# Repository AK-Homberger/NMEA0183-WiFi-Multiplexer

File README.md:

# NMEA0183 WiFi Multiplexer with ESP8266 (D1 Mini)

# Caution! 
# ----------------------------
This is an updated version (0.2) with pins changed from D7/D8 to D6/D7 to avoid boot problems (see Issues).
If you ordered already a version 1.0 PCB, then just cut the connection to D8 (e.g. with a knife) and solder a wire to D6 pin on D1 Mini. The updated software (version 0.2) will work then. But with changed serial line numbers from #1 to #2 and vice versa.
# ----------------------------

The project reads NMEA0183 messages from two serial (RS232) inputs and forwards multiplexed messages to USB-Serial and WLAN as UDP broadcast.

The multiplexer is powered either from USB connection or with 12 Volt via DC-DC converter.
ESP8266 is using Software Serial on ports D6 and D7.

Main purpose is to provide GPS and AIS information wirelessly to a tablet/smartphone for navigation.
Works with Navionics app (configure UDP connection with Host: x.y.z.255 and Port: 4444).

There is also a [software version](https://github.com/AK-Homberger/NMEA0183-WiFi-Multiplexer/tree/main/NMEA083-Parser-WiFi-Multiplexer) that is parsing the messages and can suppress certain messages. This version needs this additional NMEA0183 libray: https://github.com/ttlappalainen/NMEA0183

Just change the settings in the [programm](https://github.com/AK-Homberger/NMEA0183-WiFi-Multiplexer/blob/main/NMEA083-WiFi-Multiplexer/NMEA083-WiFi-Multiplexer.ino) according to your needs:

```
// Change these values only
// ------------------------------------------------------------------------
#define AP 0             // Set to 1 to act as Access Point, 0 as client 

const char *ssid      = "ssid";           // Set WLAN name
const char *password  = "password";      // Set password

const char *udpAddress = "192.168.4.255"; // Set network address for broadcast
const int udpPort = 4444;                 // UDP port

#define BaudRate1 4800   // Baud rate for serial#1
#define BaudRate2 38400  // Baud rate for serial#2

// -------------------------------------------------------------------------

```

KiCad files are available to change/extend and to create a [PCB](https://github.com/AK-Homberger/NMEA0183-WiFi-Multiplexer/blob/main/KiCadNMEA0183-WiFi-Multiplexer/PCB.pdf).

## Parts

- U1: [ESP8266 (D1Mini)](https://www.reichelt.de/de/en/d1-mini-esp8266-v3-0-d1-mini-p253978.html?&nbc=1)
- U2: [Max232](https://www.reichelt.de/de/en/rs232-driver-dil-16-max-232-cpe-p11216.html?&nbc=1)
- C1-C4: 4* [Capacitor 1µF](https://www.reichelt.de/de/en/tantalum-capacitor-rm-2-5-1-0-f-35-v-tantal-1-0-35-p20330.html?&nbc=1)
- J1-J3: 3* [Connector](https://www.reichelt.de/de/en/2-pin-terminal-strip-spacing-5-08-akl-101-02-p36605.html?&nbc=1)
- U3: [DC-DC Converter](https://www.reichelt.de/de/en/dc-dc-converter-5-v-1-a-single-r-78e50-10-p177268.html?&nbc=1)
- [Board](https://aisler.net/p/EZUNBBJG) @Aisler.net

## Updates
- 10.11.2022 - Version 0.3: Corrected line end handling to avaid duplication of messages sent (see Issues).
- 01.10.2021 - Version 0.2: Changed pins from D/D8 to D6/D7 to avoid boot problems (see Issues).
- 06.03.2021 - Version 0.1: Initial version

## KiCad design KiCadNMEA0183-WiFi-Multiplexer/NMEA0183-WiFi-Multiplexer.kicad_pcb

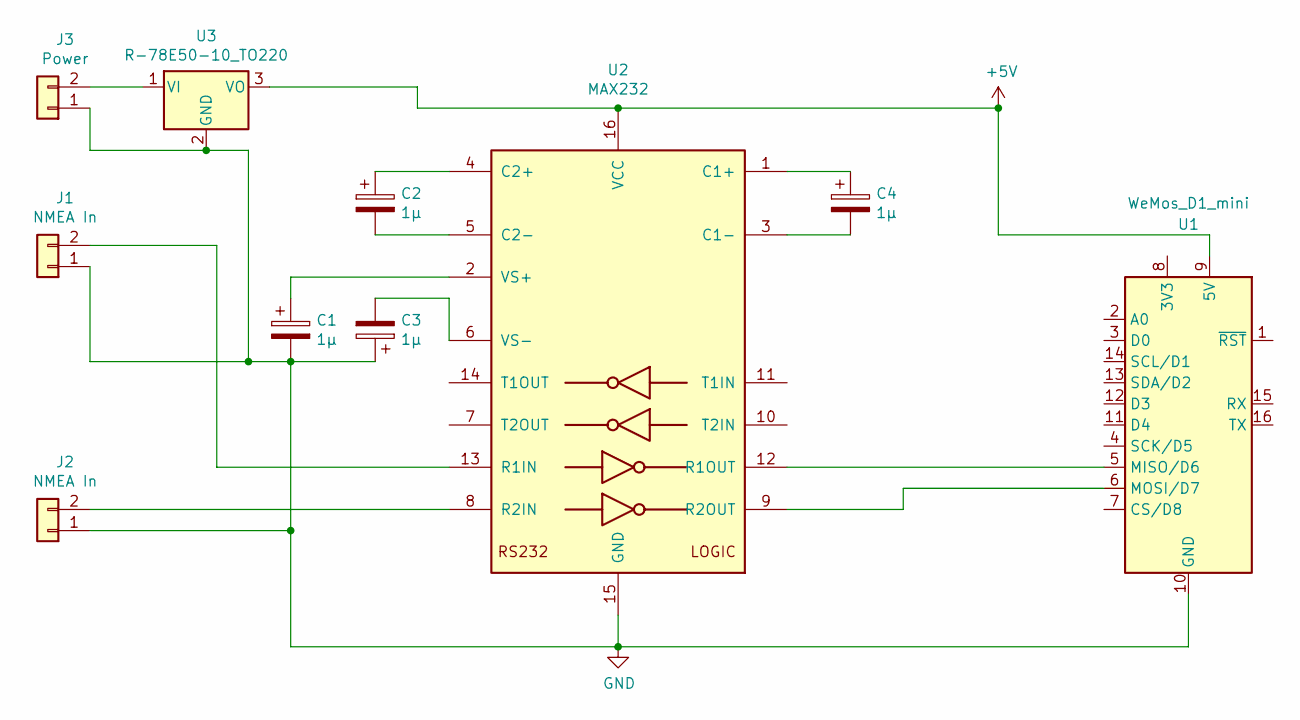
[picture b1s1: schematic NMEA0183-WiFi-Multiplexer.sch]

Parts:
C1, C2, C3, C4: 1µ; CP_Radial_D6.3mm_P2.50mm
J1, J2: NMEA In; TerminalBlock_bornier-2_P5.08mm
J3: Power; TerminalBlock_bornier-2_P5.08mm
U1: WeMos_D1_mini; WEMOS_D1_mini_light
U2: MAX232; DIP-16_W7.62mm_Socket
U3: R-78E50-10_TO220; TO-220-3_Vertical

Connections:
+5V: U1.9 (5V), U2.16 (VCC), U3.3 (VO)
GND: C1.2, C3.1, J1.1, J2.1, J3.1, U1.10 (GND), U2.15 (GND), U3.2 (GND)
unnamed: C1.1, U2.2 (VS+)
unnamed: C2.1, U2.4 (C2+)
unnamed: C2.2, U2.5 (C2-)
unnamed: C3.2, U2.6 (VS-)
unnamed: C4.1, U2.1 (C1+)
unnamed: C4.2, U2.3 (C1-)
unnamed: J1.2, U2.13 (R1IN)
unnamed: J2.2, U2.8 (R2IN)
unnamed: J3.2, U3.1 (VI)
unnamed: U1.5 (MISO/D6), U2.12 (R1OUT)
unnamed: U1.6 (MOSI/D7), U2.9 (R2OUT)

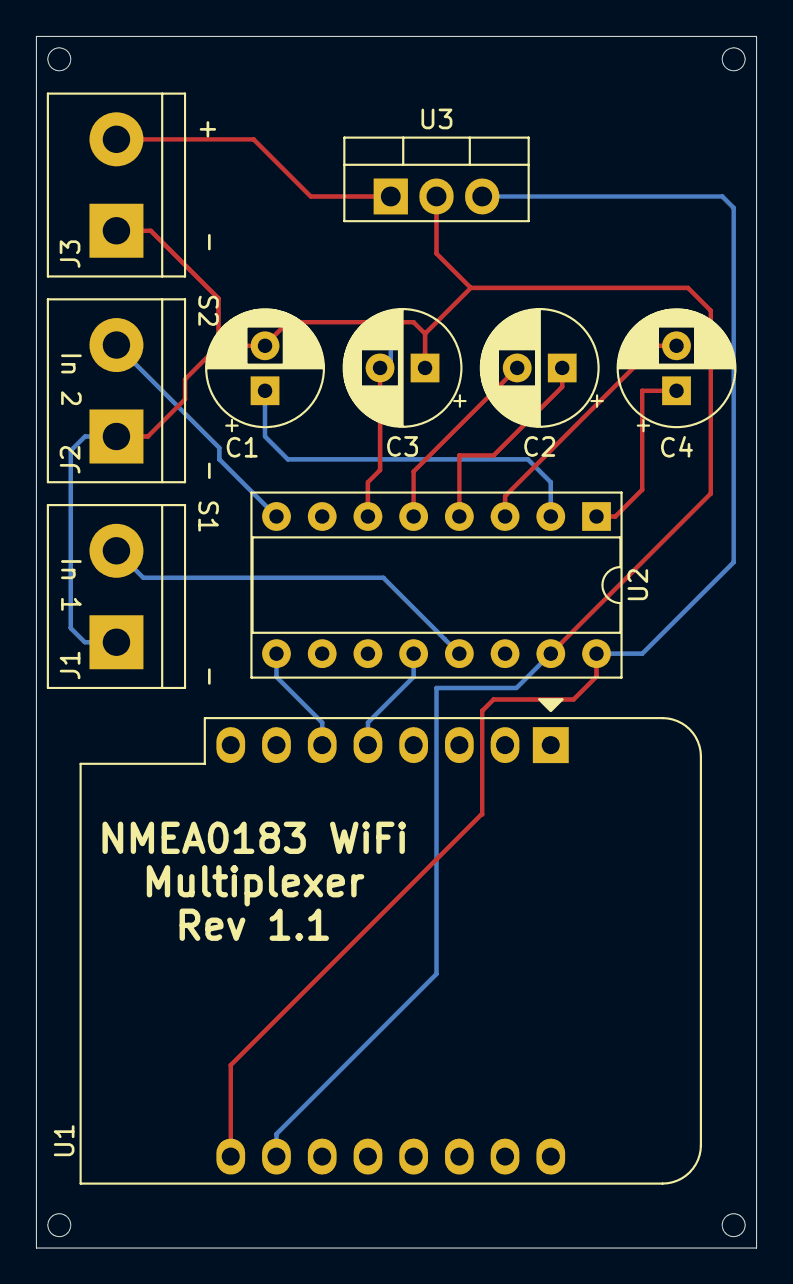
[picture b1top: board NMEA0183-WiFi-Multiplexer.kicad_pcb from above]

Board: 2 copper layers, 40.0 x 67.3 mm, 10 parts (0 on the bottom side), 13 nets.

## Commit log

2021-10-01 Changed to D6/D7 input pins to avoid boot problems (see Issues)
2021-10-01 Version 1.1 (Changed to D7/D2 pins to avoid boot problems).
2021-10-01 Cahnged pins from D7/D8 to D6/D7.
2022-11-10 Corrected line end handling.
2022-11-10 Deleted additional New Line.
